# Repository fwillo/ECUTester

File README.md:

# BremerECU Production Tester

BremerECU Production Tester is a Flutter desktop application for initial PCBA programming and final production testing. It first guides the operator through TC2030 JTAG/SWD connection and flashes the initial firmware and default calibration with STM32CubeProgrammer CLI. It then connects to a BremerECU-compatible board over UART, samples selected ECU output channels, shows live measurements during collection, and produces a clear PASS or FAIL result for the operator.

The tool is designed for a production bench: program the bare board, select the detected tester UART, watch live values while the sample set is collected, and record the result with a numbered CSV log for traceability.

## Features

- Lists only the intended USB serial device: VID `0483`, PID `5740`.
- Shows the TC2030 connection graphic before programming.
- Lets the operator select the `STM32_Programmer_CLI` executable, firmware binary, default calibration binary, debug interface, and flash address.
- Reads the STM32F767 96-bit unique device ID over SWD/JTAG before programming.
- Programs via STM32CubeProgrammer CLI in one session: firmware, then the default calibration to `0x08100000` (sector 8) and a backup copy to `0x08140000` (sector 9), each verified, followed by a reset.
- Rejects a calibration larger than one 256 KB sector, or firmware that would overlap the calibration sectors.
- Connects at `115200 8N1`.
- Requests ECU output-channel data on a 10 Hz schedule, limited by UART response time.
- Collects `100` frames per test.
- Shows a live dashboard for:
  - RPM
  - CLT
  - MAP
  - Accelerator Pedal
  - VBatt
  - IAT
- Validates averages against configured production limits.
- Displays a high-visibility PASS/FAIL result screen.
- Shows failure reasons when a metric is outside range.
- Saves every completed test as an iteratively numbered CSV log per connected device.

## Test Limits

The current pass criteria are configured in [lib/ecu_protocol.dart](lib/ecu_protocol.dart):

| Metric | Passing average range |
| --- | ---: |
| RPM | `>= 990 and <= 1010 RPM` |
| CLT | `>= 66.6 and <= 67.8 C` |
| MAP | `>= 45.0 and <= 45.8 kPa` |
| Accelerator Pedal | `>= 12.0 and <= 14.0 %` |
| VBatt | `> 11.00 and < 13.00 V` |
| IAT | `> 5.0 and < 6.0 C` |

A test passes only when all metric averages are inside their configured ranges.

## Operator Workflow

1. Connect the TC2030 cable to the bare board as shown in the application.
2. Start the application.
3. Select the STM32CubeProgrammer CLI executable if the default path is not correct.
4. Select the initial firmware `.bin` file and the default calibration `.bin` file. Both paths are remembered for the next start (`~/Library/Application Support/BremerECU Production Tester/settings.json` on macOS).
5. Confirm the debug interface and flash address, then run programming. The app reads the STM32F767 unique ID before flashing and aborts if the ID cannot be read.
6. For an already programmed board, use **Test Already Programmed** to skip flashing.
7. After programming succeeds, or after skipping programming, connect the PCBA/tester UART and continue to the UART test.
8. Select the listed UART device.
9. Wait while the live dashboard collects 100 frames.
10. Read the final PASS or FAIL result.
11. If the result is FAIL, review the displayed failure reasons.

The result screen also shows the saved CSV path for the completed test.

## Log Files

Each programming attempt that successfully reads an MCU unique ID is saved automatically as a CSV file under:

```text
~/Documents/BremerECU Production Tester Logs/<device>/programming_0001.csv
```

Subsequent programming attempts for the same MCU are saved as:

```text
programming_0002.csv
programming_0003.csv
...
```

The programming `<device>` folder uses the STM32F767 96-bit unique device ID read from address `0x1FF0F420` before flashing. If the ID cannot be read, no programming log is written because the target is probably not connected correctly.

Each completed test is saved automatically as a CSV file under:

```text
~/Documents/BremerECU Production Tester Logs/<device>/test_0001.csv
```

Subsequent tests for the same device are saved as:

```text
test_0002.csv
test_0003.csv
...
```

The device folder uses the USB serial number when available. If no serial number is exposed, the app falls back to VID, PID, and port name.

Each CSV contains:

- log index
- start and completion timestamps
- PASS/FAIL result
- device metadata
- failure reasons, if any
- metric averages
- all collected frame values

The log-writing code lives in [lib/test_log_writer.dart](lib/test_log_writer.dart).

## Serial Protocol

The app sends the ECU output-channel request command `O` with offset `0` and length `1397`.

Request format:

```text
00 05 4F <offset:u16-le> <length:u16-le> <crc32:u32-be>
```

Response format currently handled by the app:

```text
<body length:u16-be> <status:u8> <1397-byte output payload> <crc32:u32-be>
```

For the configured request, the expected response is:

```text
05 76 <1398-byte body> <4-byte CRC>
```

The response CRC is validated before any metrics are parsed.

## Development

Install Flutter and ensure macOS desktop support is enabled. This project uses:

- `flutter_libserialport`
- `crc32_checksum`
- `file_selector`

Fetch dependencies:

```bash
flutter pub get
```

Run on macOS:

```bash
flutter run -d macos
```

Build a debug macOS app:

```bash
flutter build macos --debug
```

Build a release macOS app:

```bash
flutter build macos --release
```

Run checks:

```bash
flutter analyze
flutter test
```

## GitHub Builds

The repository includes a GitHub Actions workflow at:

```text
.github/workflows/build-desktop.yml
```

It builds:

- macOS release app
- Windows x64 release app

Each workflow run uploads zipped build artifacts. In GitHub, open the workflow run and download them from the **Artifacts** section.

Pushing a version tag also creates a GitHub Release with the macOS and Windows zip files attached:

```bash
git tag v1.0.0
git push origin v1.0.0
```

## macOS Notes

The app name shown in the macOS title bar is configured in:

```text
macos/Runner/Configs/AppInfo.xcconfig
```

The macOS sandbox is disabled for this tool because serial device access requires direct access to `/dev/cu.*` or `/dev/tty.*` devices.

`flutter_libserialport` currently emits a Flutter warning about Swift Package Manager support. The app builds through CocoaPods.

## Project Structure

```text
lib/main.dart                               App entry point, theme, and shared library wiring
lib/initial_programming.dart                STM32CubeProgrammer CLI command building and execution
lib/programming_log_writer.dart             Programming CSV log persistence and per-device numbering
lib/ecu_protocol.dart                       ECU request/response protocol, frame parsing, pass/fail rules
lib/test_log_writer.dart                    CSV log persistence and per-device numbering
lib/src/serial_transport.dart               Serial port abstractions and libserialport implementation
lib/src/screens/initial_programming_screen.dart
lib/src/screens/uart_selection_screen.dart
lib/src/screens/data_collection_screen.dart
lib/src/screens/test_result_screen.dart
lib/src/widgets/shared_widgets.dart         Small shared UI widgets
test/                                       Protocol, programming, and log writer tests
macos/                                      macOS desktop runner configuration
```

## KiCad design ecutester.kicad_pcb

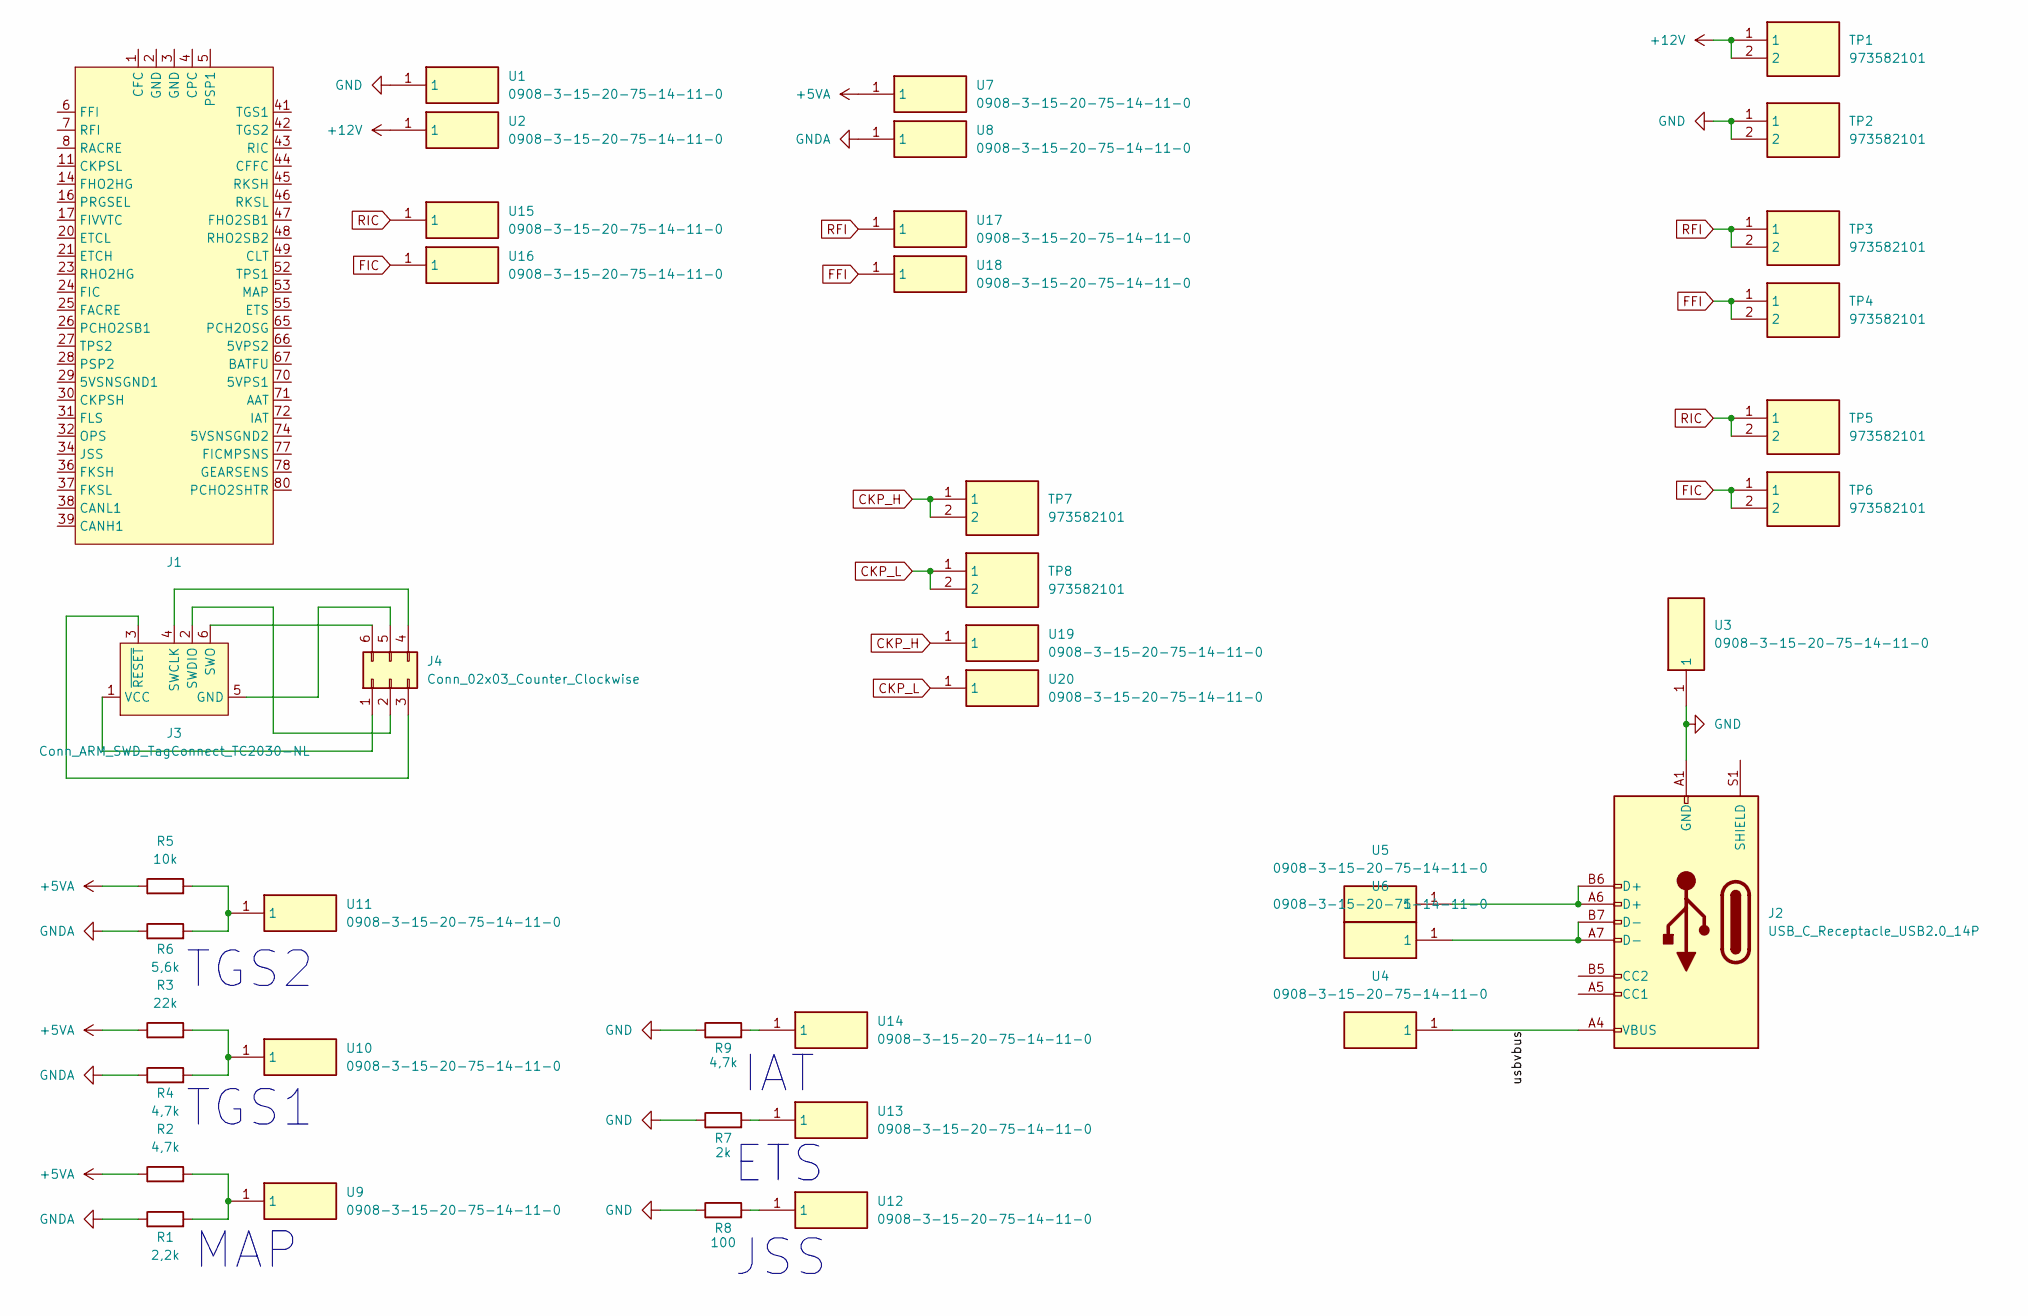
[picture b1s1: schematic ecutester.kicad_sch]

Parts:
J1: HDCustomCase81
J2: USB_C_Receptacle_USB2.0_14P; USB_C_Receptacle_GCT_USB4110
J3: Conn_ARM_SWD_TagConnect_TC2030-NL; Tag-Connect_TC2030-IDC-NL_2x03_P1.27mm_Vertical
J4: Conn_02x03_Counter_Clockwise; IDC-Header_2x03_P2.54mm_Horizontal
R1: 2,2k; R_0402_1005Metric
R2, R4, R9: 4,7k; R_0402_1005Metric
R3: 22k; R_0402_1005Metric
R5: 10k; R_0402_1005Metric
R6: 5,6k; R_0402_1005Metric
R7: 2k; R_0402_1005Metric
R8: 100; R_0402_1005Metric
TP1, TP2, TP3, TP4, TP5, TP6, TP7, TP8: 973582101; Mouser Part Number 845-973582101
U1, U2, U3, U4, U5, U6, U7, U8, U9, U10, U11, U12, U13, U14, U15, U16, U17, U18, U19, U20: 0908-3-15-20-75-14-11-0; 0908315207514110; Mouser Part Number 575-0908315207514

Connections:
+5VA: R2.1, R3.1, R5.1, U7.1
+12V: TP1.1, TP1.2, U2.1
/usbvbus: J2.A4 (VBUS), J2.A9 (VBUS), J2.B4 (VBUS), J2.B9 (VBUS), U4.1
CKP_H: TP7.1, TP7.2, U19.1
CKP_L: TP8.1, TP8.2, U20.1
FFI: TP4.1, TP4.2, U18.1
FIC: TP6.1, TP6.2, U16.1
GND: J2.A1 (GND), J2.A12 (GND), J2.B1 (GND), J2.B12 (GND), R7.1, R8.1, R9.1, TP2.1, TP2.2, U1.1, U3.1
GNDA: R1.1, R4.1, R6.1, U8.1
unnamed: J2.A6 (D+), J2.B6 (D+), U5.1
unnamed: J2.A7 (D-), J2.B7 (D-), U6.1
unnamed: J3.5 (GND), J4.5
unnamed: J3.4 (SWCLK), J4.4
unnamed: J3.2 (SWDIO), J4.2
unnamed: J3.6 (SWO), J4.6
unnamed: J3.1 (VCC), J4.1
unnamed: J3.3 (~RESET), J4.3
unnamed: R1.2, R2.2, U9.1
unnamed: R3.2, R4.2, U10.1
unnamed: R5.2, R6.2, U11.1
unnamed: R7.2, U13.1
unnamed: R8.2, U12.1
unnamed: R9.2, U14.1
RFI: TP3.1, TP3.2, U17.1
RIC: TP5.1, TP5.2, U15.1

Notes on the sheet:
JSS
IAT
ETS
TGS1
TGS2
MAP

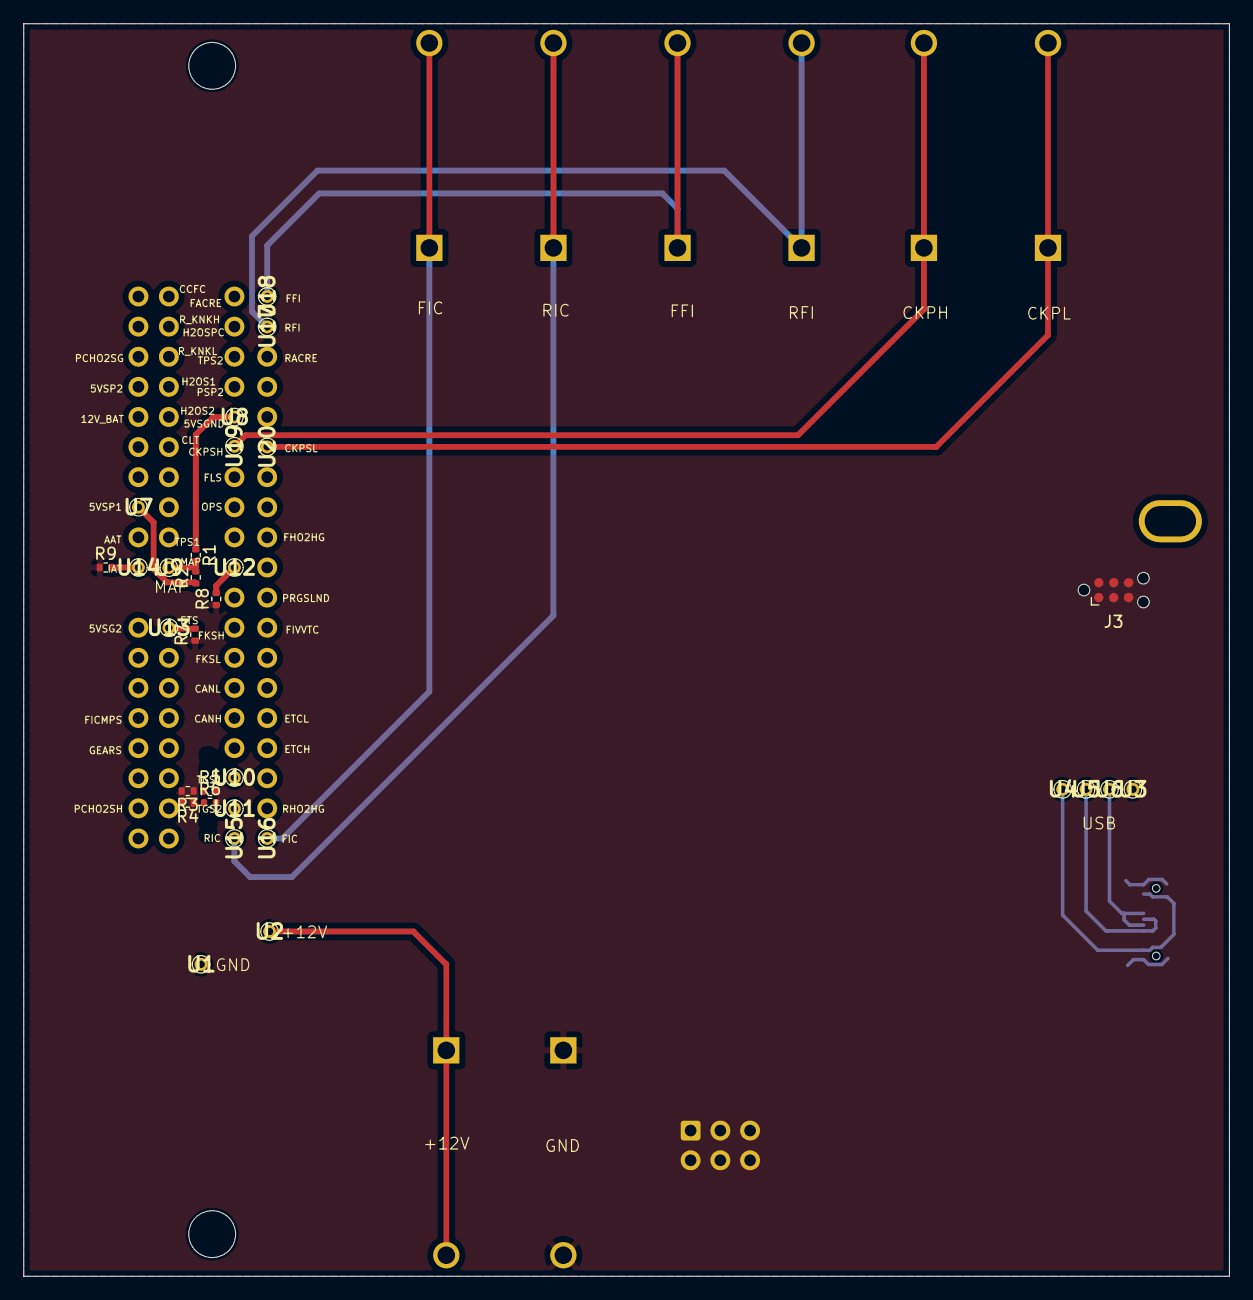
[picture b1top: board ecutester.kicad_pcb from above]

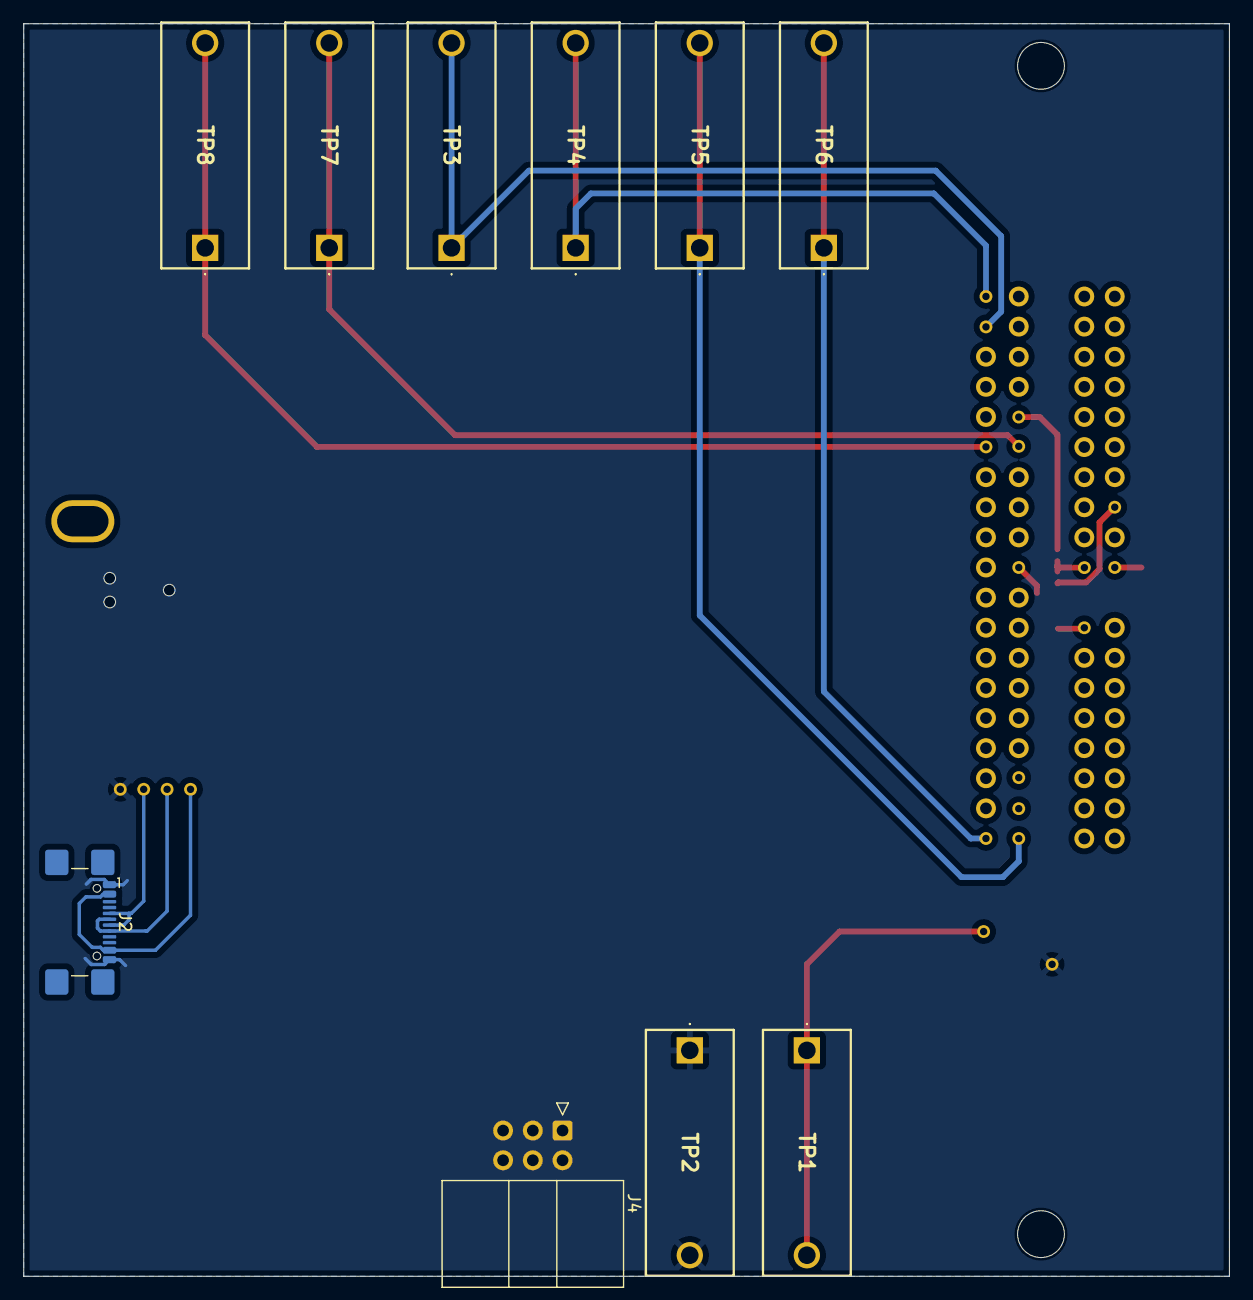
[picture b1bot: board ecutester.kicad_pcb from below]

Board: 2 copper layers, 103.0 x 107.0 mm, 41 parts (11 on the bottom side), 25 nets.
